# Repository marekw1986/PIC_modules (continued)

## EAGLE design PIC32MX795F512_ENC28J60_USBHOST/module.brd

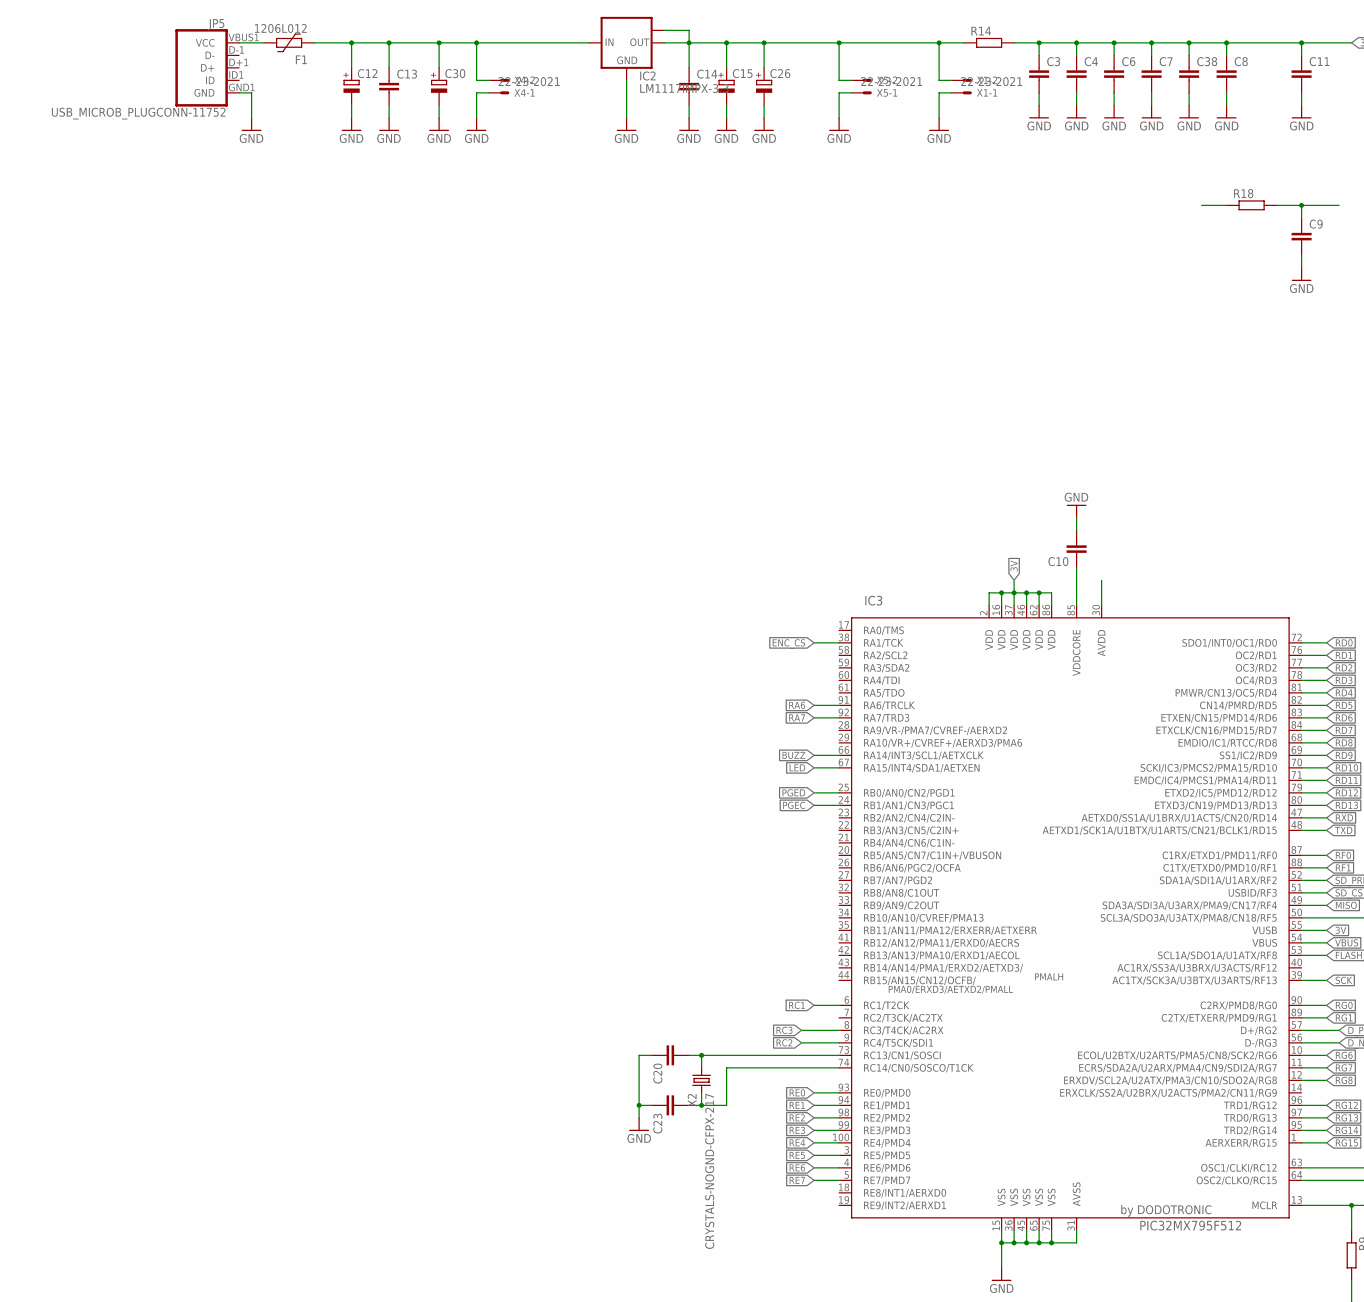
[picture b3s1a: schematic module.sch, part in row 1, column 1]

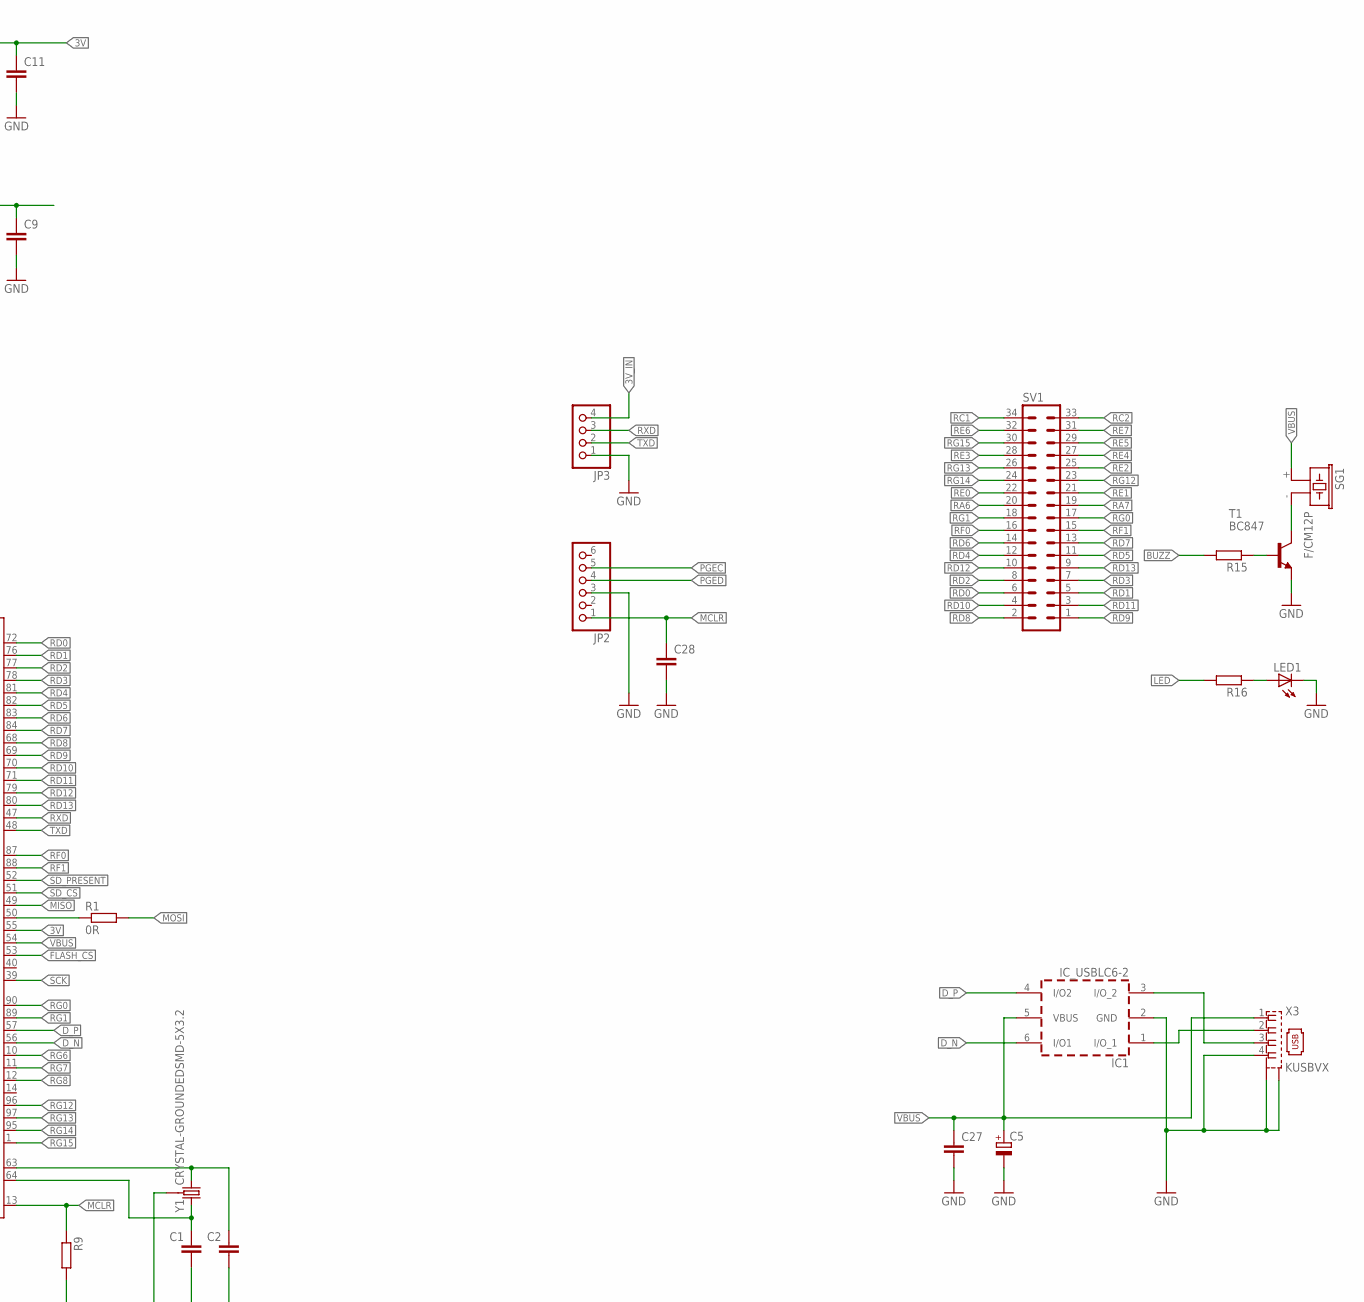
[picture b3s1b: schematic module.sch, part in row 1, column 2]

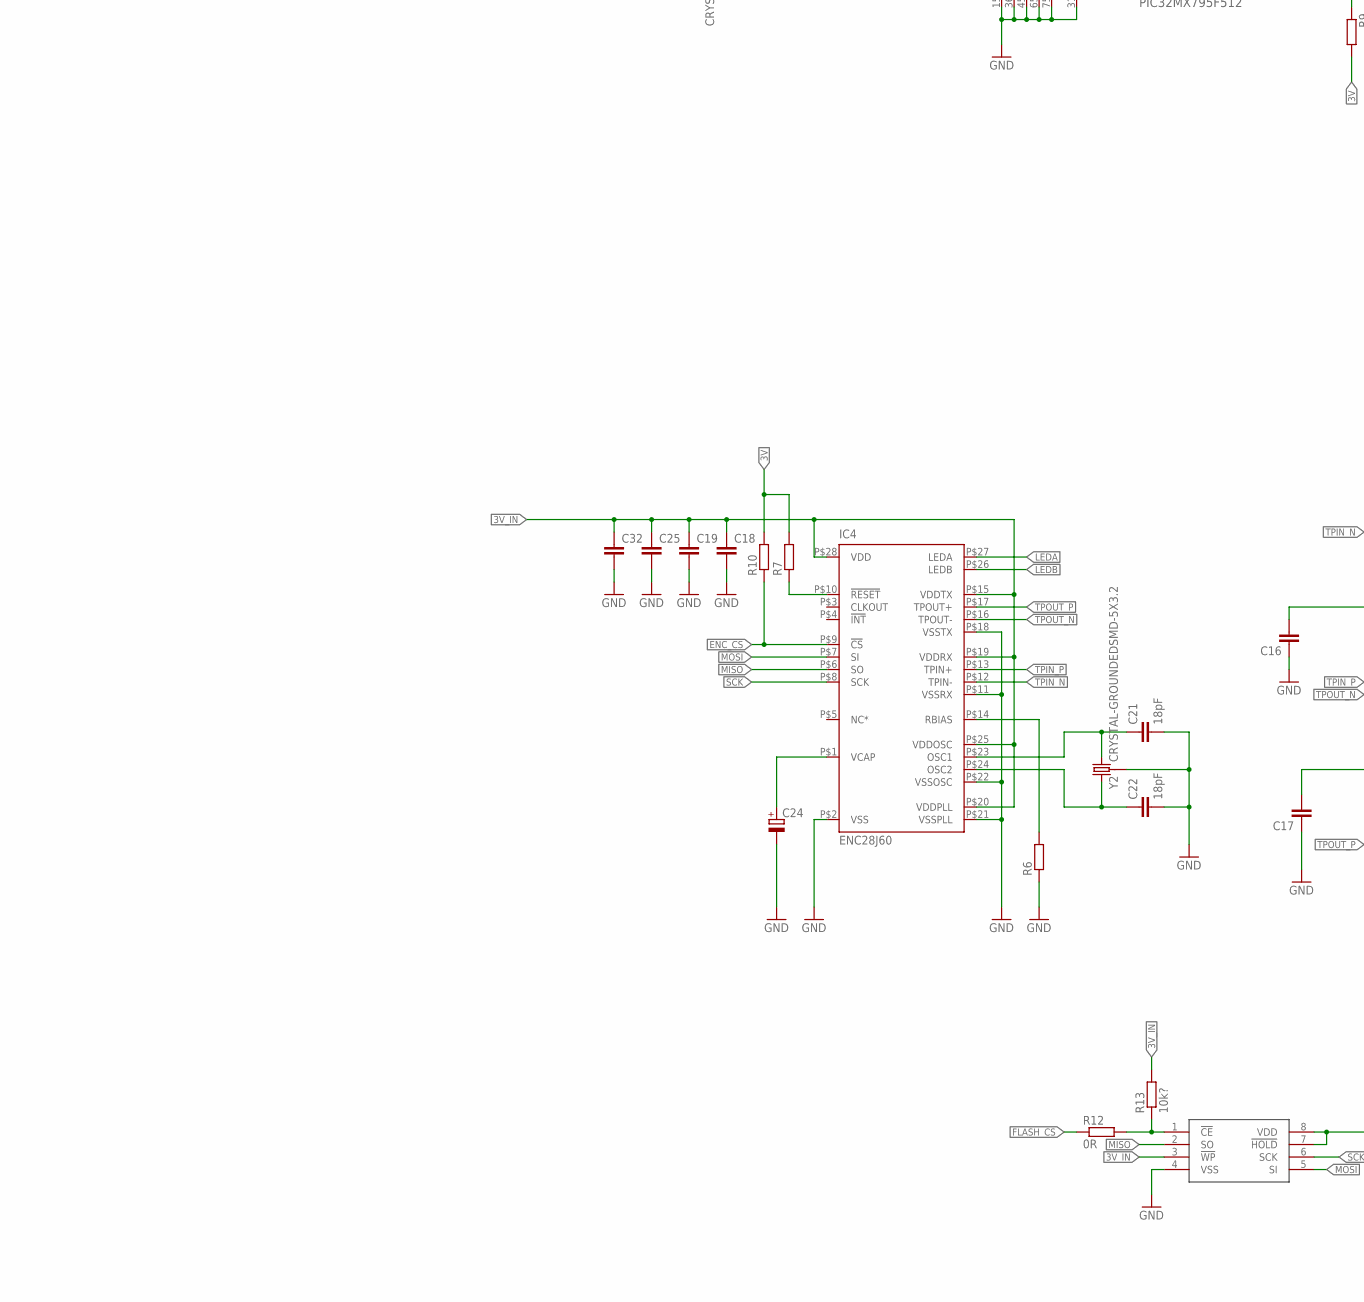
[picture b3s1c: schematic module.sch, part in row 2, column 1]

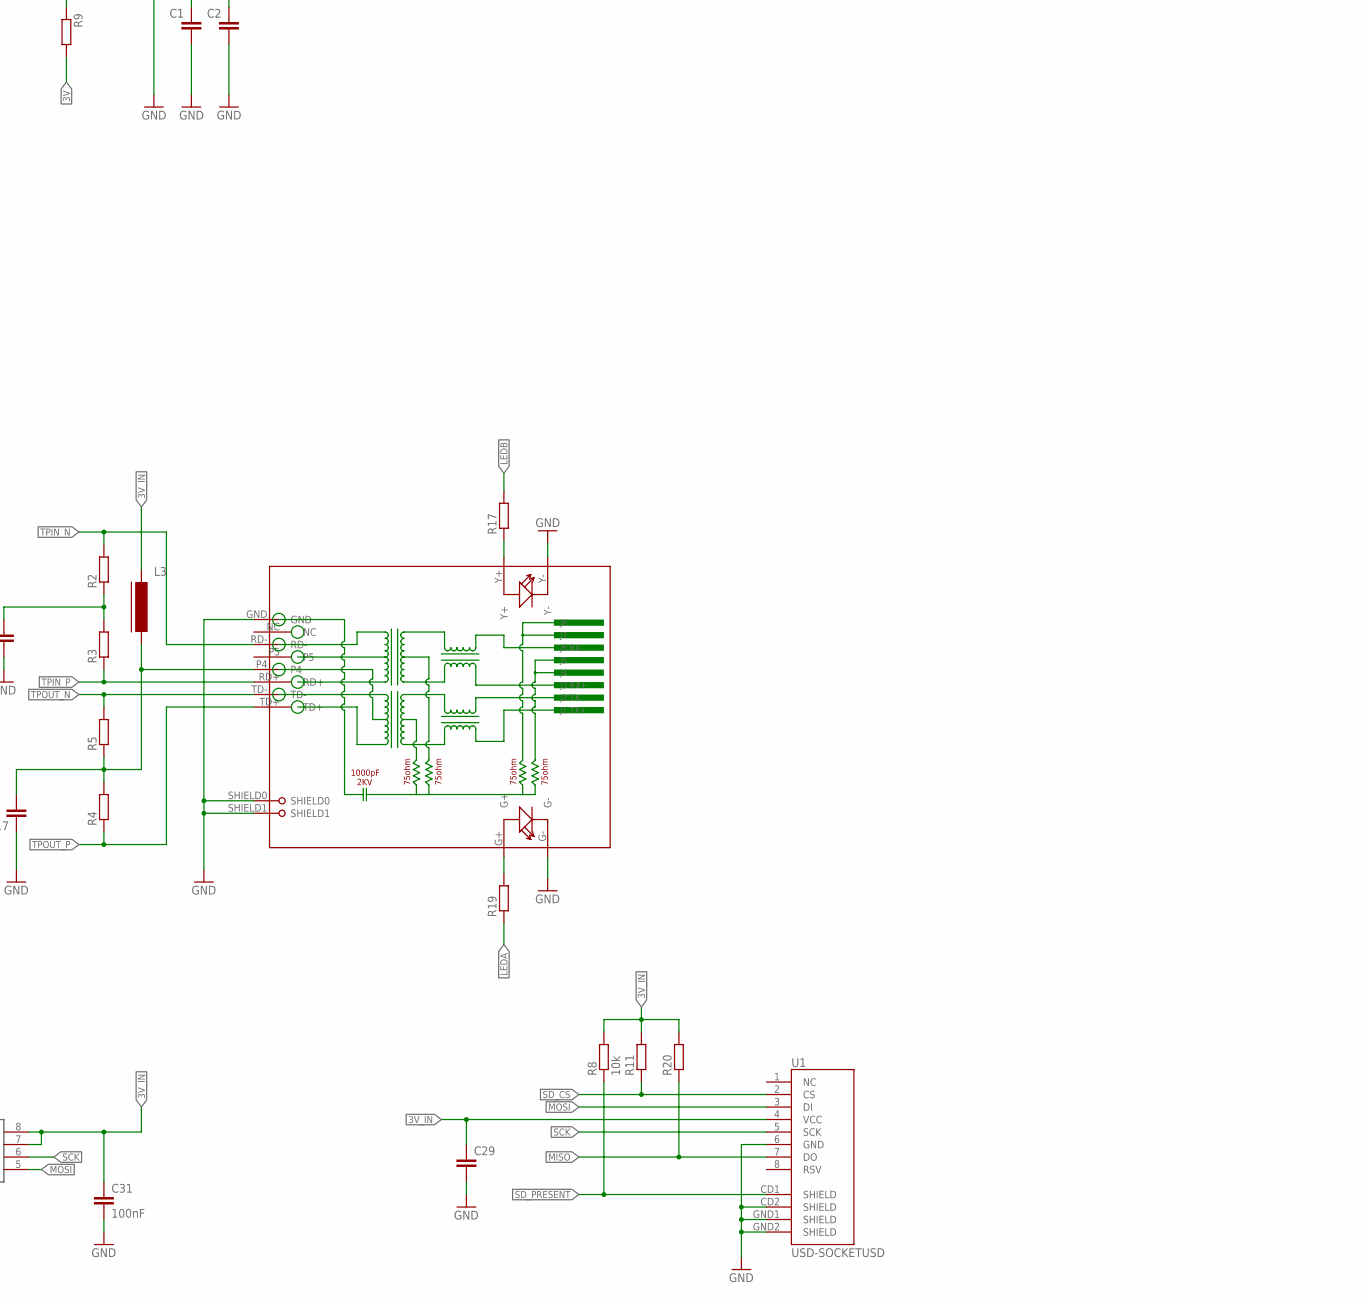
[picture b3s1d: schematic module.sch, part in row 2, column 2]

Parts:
C1, C2, C10, C13, C14, C16, C17, C19, C20, C23, C25, C27, C28, C29, C38: C-EUC0603; C0603
C3, C4, C6, C7, C8, C9, C11, C18, C32: C-EUC0402; C0402
C5, C24, C26, C30: CPOL-EUSMCA; SMC_A
C12, C15: CPOL-EUSMCB; SMC_B
C21, C22: 18pF; C0603
C31: 100nF; C0603
F1: 1206L012; 1206L
IC1: IC_USBLC6-2; SOT-23-6L
IC2: LM1117IMPX-3.3; SOT223
IC3: PIC32MX795F512; TQFP100_12X12
IC4: ENC28J60; TSSOP28W
JP2: PINHD-1X6; 1X06
JP3: PINHD-1X4; 1X04
JP5: USB_MICROB_PLUGCONN-11752; USB-B-MICRO-SMD_V03
L3: FERRITE-0805; FB805
LED1: LED3MM
R1, R12: 0R; R0603
R2, R3, R4, R5, R9, R10, R11, R15, R16, R20: R-EU_R0603; R0603
R6, R18: R-EU_R0805; R0805
R7: R-EU_R0402; R0402
R8: 10k; R0603
R13: 10k?; R0603
R14, R17, R19: R-EU_R1206; R1206
RJ1: HR911105A
SG1: F/CM12P
SV1: ML34L
T1: BC847; SOT23
U1: USD-SOCKETUSD; USD-SOCKET-PP
U$2: SST25VF016BSO8M; SO-08M
X1, X4, X5: 22-23-2021
X2: CRYSTALS-NOGND-CFPX-217; 3.2X1.5-2-PAD
X3: KUSBVX
Y1, Y2: CRYSTAL-GROUNDEDSMD-5X3.2; CRYSTAL-SMD-5X3.2-4PAD

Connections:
3V: C3.1, C4.1, C6.1, C7.1, C8.1, C11.1, C38.1, IC3.2 (VDD), IC3.16 (VDD), IC3.37 (VDD), IC3.46 (VDD), IC3.55 (VUSB), IC3.62 (VDD), IC3.86 (VDD), R7.2, R9.2, R10.2, R14.2, R18.1
3V_IN: C14.1, C15.+, C18.1, C19.1, C25.1, C26.+, C29.1, C31.1, C32.1, IC2.2 (OUT), IC2.TAB (OUT1), IC4.P$15 (VDDTX), IC4.P$19 (VDDRX), IC4.P$20 (VDDPLL), IC4.P$25 (VDDOSC), IC4.P$28 (VDD), JP3.4, L3.1, R8.2, R11.2, R13.2, R14.1, R20.2, U1.4 (VCC), U$2.3 (!WP), U$2.7 (!HOLD), U$2.8 (VDD), X1.2, X5.2
AN_3V: C9.1, IC3.30 (AVDD), R18.2
BUZZ: IC3.66 (RA14/INT3/SCL1/AETXCLK), R15.2
CE1: R12.2, R13.1, U$2.1 (!CE)
D2_N: IC1.1 (I/O_1), X3.2
D2_P: IC1.3 (I/O_2), X3.3
D_N: IC1.6 (I/O1), IC3.56 (D-/RG3)
D_P: IC1.4 (I/O2), IC3.57 (D+/RG2)
ENC_CS: IC3.38 (RA1/TCK), IC4.P$9 (!CS), R10.1
ENC_RST: IC4.P$10 (!RESET), R7.1
FLASH_CS: IC3.53 (SCL1A/SDO1A/U1ATX/RF8), R12.1
GND: C1.2, C2.2, C3.2, C4.2, C5.-, C6.2, C7.2, C8.2, C9.2, C10.2, C11.2, C12.-, C13.2, C14.2, C15.-, C16.1, C17.1, C18.2, C19.2, C20.1, C21.2, C22.2, C23.1, C24.-, C25.2, C26.-, C27.2, C28.2, C29.2, C30.-, C31.2, C32.2, C38.2, IC1.2 (GND), IC2.1 (GND), IC3.15 (VSS), IC3.31 (AVSS), IC3.36 (VSS), IC3.45 (VSS), IC3.65 (VSS), IC3.75 (VSS), IC4.P$2 (VSS), IC4.P$11 (VSSRX), IC4.P$18 (VSSTX), IC4.P$21 (VSSPLL), IC4.P$22 (VSSOSC), JP2.3, JP3.1, JP5.GND1 (GND), LED1.K (C), R6.1, RJ1.G-, RJ1.GND, RJ1.SHIELD0, RJ1.SHIELD1, RJ1.Y-, T1.2 (E), U1.6 (GND), U1.CD2 (SHIELD), U1.GND1 (SHIELD), U1.GND2 (SHIELD), U$2.4 (VSS), X1.1, X3.4, X3.M1 (S1), X3.M2 (S2), X4.1, X5.1, Y1.2 (3), Y1.4 (3), Y2.2 (3), Y2.4 (3)
LED: IC3.67 (RA15/INT4/SDA1/AETXEN), R16.2
LEDA: IC4.P$27 (LEDA), R19.1
LEDB: IC4.P$26 (LEDB), R17.2
MCLR: C28.1, IC3.13 (MCLR), JP2.1, R9.1
MISO: IC3.49 (SDA3A/SDI3A/U3ARX/PMA9/CN17/RF4), IC4.P$6 (SO), R20.1, U1.7 (DO), U$2.2 (SO)
MOSI: IC4.P$7 (SI), R1.2, U1.3 (DI), U$2.5 (SI)
unnamed: SG1.- (2), T1.3 (C)
unnamed: C16.2, R2.1, R3.2
unnamed: R15.1, T1.1 (B)
unnamed: LED1.A, R16.1
unnamed: IC3.50 (SCL3A/SDO3A/U3ATX/PMA8/CN18/RF5), R1.1
unnamed: C17.2, L3.2, R4.2, R5.1, RJ1.P4
unnamed: C10.1, IC3.85 (VDDCORE)
unnamed: IC4.P$14 (RBIAS), R6.2
unnamed: F1.1, JP5.VBUS1 (VCC)
unnamed: C21.1, IC4.P$23 (OSC1), Y2.1 (2)
unnamed: C22.1, IC4.P$24 (OSC2), Y2.3 (1)
unnamed: C24.+, IC4.P$1 (VCAP)
unnamed: R17.1, RJ1.Y+
unnamed: R19.2, RJ1.G+
OSC1: C2.1, IC3.63 (OSC1/CLKI/RC12), Y1.1 (2)
OSC2: C1.1, IC3.64 (OSC2/CLKO/RC15), Y1.3 (1)
PGEC: IC3.24 (RB1/AN1/CN3/PGC1), JP2.5
PGED: IC3.25 (RB0/AN0/CN2/PGD1), JP2.4
RA6: IC3.91 (RA6/TRCLK), SV1.20
RA7: IC3.92 (RA7/TRD3), SV1.19
RC1: IC3.6 (RC1/T2CK), SV1.34
RC2: IC3.9 (RC4/T5CK/SDI1), SV1.33
RC3: IC3.8 (RC3/T4CK/AC2RX)
RD0: IC3.72 (SDO1/INT0/OC1/RD0), SV1.6
RD1: IC3.76 (OC2/RD1), SV1.5
RD2: IC3.77 (OC3/RD2), SV1.8
RD3: IC3.78 (OC4/RD3), SV1.7
RD4: IC3.81 (PMWR/CN13/OC5/RD4), SV1.12
RD5: IC3.82 (CN14/PMRD/RD5), SV1.11
RD6: IC3.83 (ETXEN/CN15/PMD14/RD6), SV1.14
RD7: IC3.84 (ETXCLK/CN16/PMD15/RD7), SV1.13
RD8: IC3.68 (EMDIO/IC1/RTCC/RD8), SV1.2
RD9: IC3.69 (SS1/IC2/RD9), SV1.1
RD10: IC3.70 (SCKI/IC3/PMCS2/PMA15/RD10), SV1.4
RD11: IC3.71 (EMDC/IC4/PMCS1/PMA14/RD11), SV1.3
RD12: IC3.79 (ETXD2/IC5/PMD12/RD12), SV1.10
RD13: IC3.80 (ETXD3/CN19/PMD13/RD13), SV1.9
RE0: IC3.93 (RE0/PMD0), SV1.22
RE1: IC3.94 (RE1/PMD1), SV1.21
RE2: IC3.98 (RE2/PMD2), SV1.25
RE3: IC3.99 (RE3/PMD3), SV1.28
RE4: IC3.100 (RE4/PMD4), SV1.27
RE5: IC3.3 (RE5/PMD5), SV1.29
RE6: IC3.4 (RE6/PMD6), SV1.32
RE7: IC3.5 (RE7/PMD7), SV1.31
RF0: IC3.87 (C1RX/ETXD1/PMD11/RF0), SV1.16
RF1: IC3.88 (C1TX/ETXD0/PMD10/RF1), SV1.15
RG0: IC3.90 (C2RX/PMD8/RG0), SV1.17
RG1: IC3.89 (C2TX/ETXERR/PMD9/RG1), SV1.18
RG6: IC3.10 (ECOL/U2BTX/U2ARTS/PMA5/CN8/SCK2/RG6)
RG7: IC3.11 (ECRS/SDA2A/U2ARX/PMA4/CN9/SDI2A/RG7)
RG8: IC3.12 (ERXDV/SCL2A/U2ATX/PMA3/CN10/SDO2A/RG8)
RG12: IC3.96 (TRD1/RG12), SV1.23
RG13: IC3.97 (TRD0/RG13), SV1.26
RG14: IC3.95 (TRD2/RG14), SV1.24
RG15: IC3.1 (AERXERR/RG15), SV1.30
RXD: IC3.47 (AETXD0/SS1A/U1BRX/U1ACTS/CN20/RD14), JP3.3
SCK: IC3.39 (AC1TX/SCK3A/U3BTX/U3ARTS/RF13), IC4.P$8 (SCK), U1.5 (SCK), U$2.6 (SCK)
SD_CS: IC3.51 (USBID/RF3), R11.1, U1.2 (CS)
SD_PRESENT: IC3.52 (SDA1A/SDI1A/U1ARX/RF2), R8.1, U1.CD1 (SHIELD)
SOSCI: C20.2, IC3.73 (RC13/CN1/SOSCI), X2.1
SOSCO: C23.2, IC3.74 (RC14/CN0/SOSCO/T1CK), X2.2
TPIN_N: IC4.P$12 (TPIN-), R2.2, RJ1.RD-
TPIN_P: IC4.P$13 (TPIN+), R3.1, RJ1.RD+
TPOUT_N: IC4.P$16 (TPOUT-), R5.2, RJ1.TD-
TPOUT_P: IC4.P$17 (TPOUT+), R4.1, RJ1.TD+
TXD: IC3.48 (AETXD1/SCK1A/U1BTX/U1ARTS/CN21/BCLK1/RD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), JP3.2
VBUS: C5.+, C12.+, C13.1, C27.1, C30.+, F1.2, IC1.5 (VBUS), IC2.3 (IN), IC3.54 (VBUS), SG1.+ (1), X3.1, X4.2

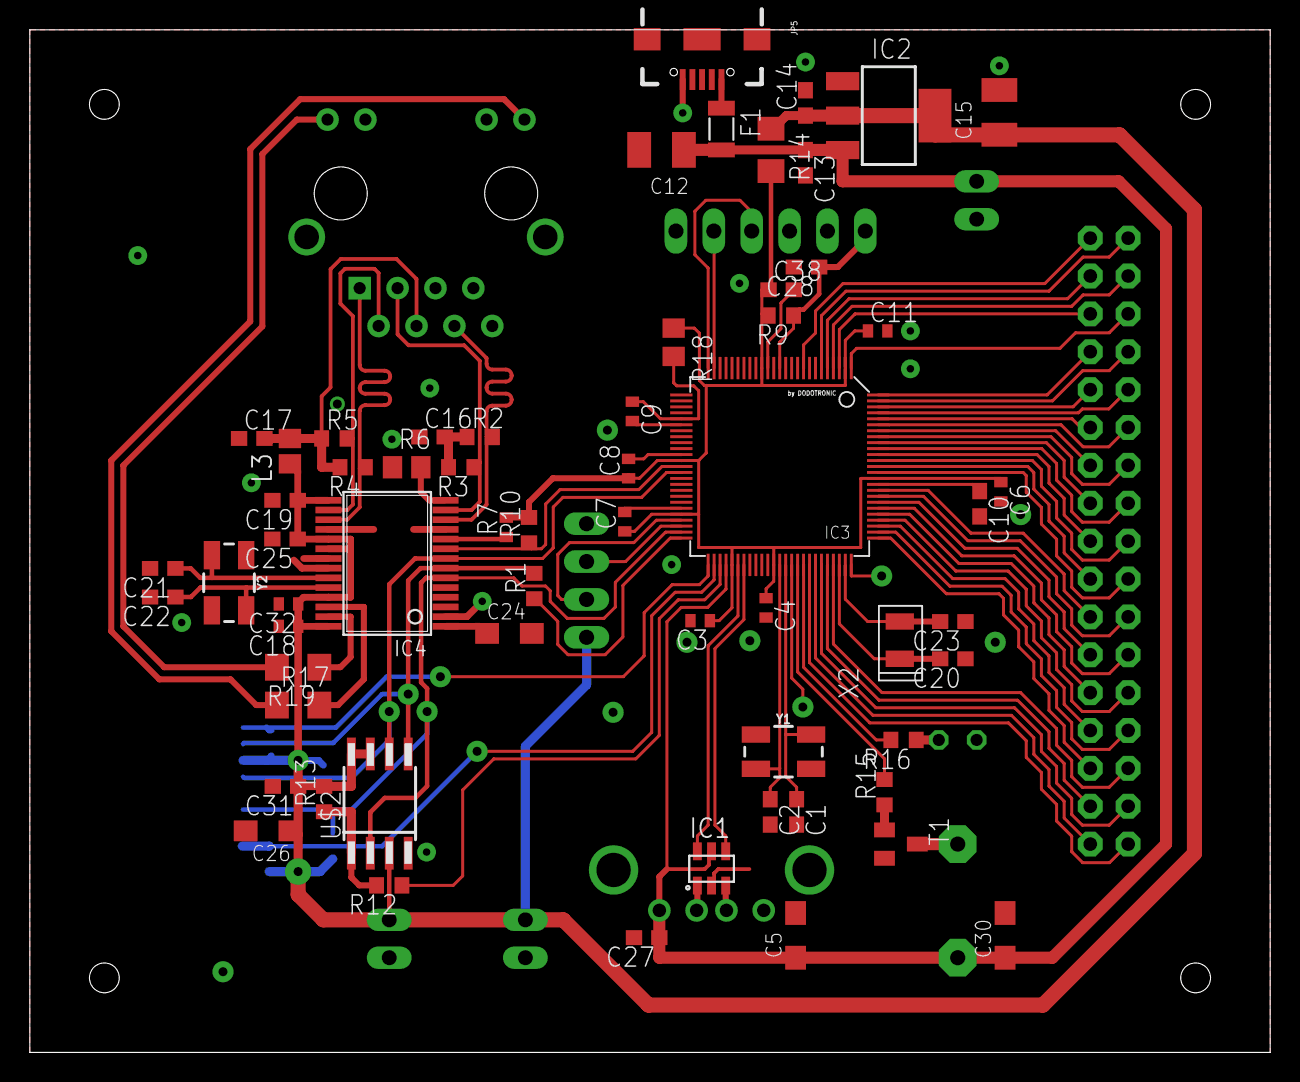
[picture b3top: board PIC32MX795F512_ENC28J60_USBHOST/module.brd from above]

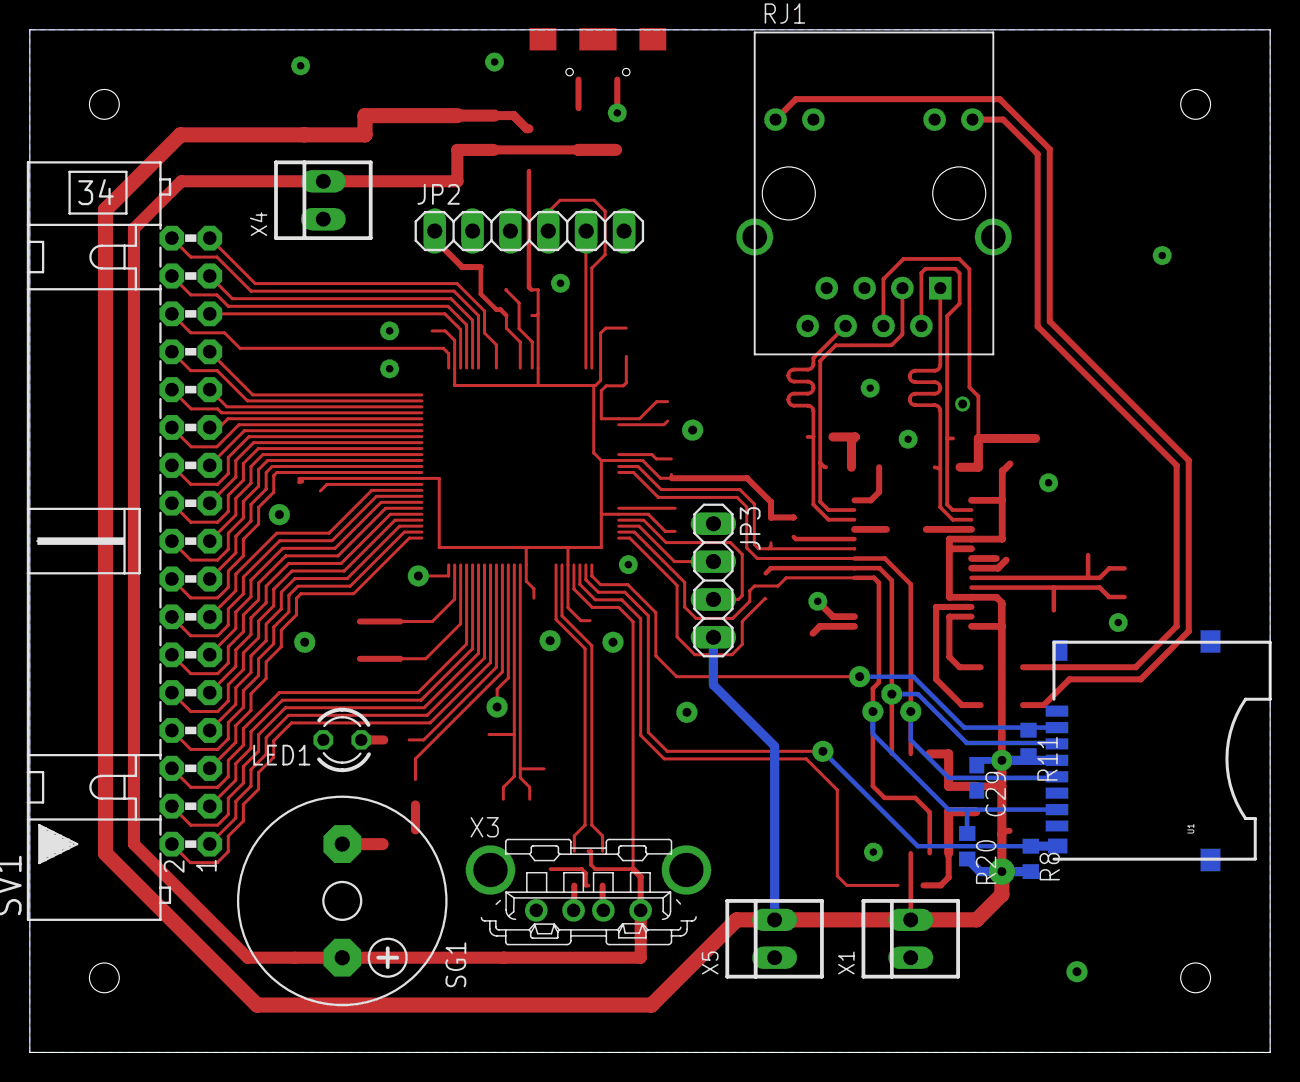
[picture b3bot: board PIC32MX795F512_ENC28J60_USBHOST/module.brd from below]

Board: 2 copper layers, 83.2 x 68.6 mm, 76 parts (15 on the bottom side), 83 nets.

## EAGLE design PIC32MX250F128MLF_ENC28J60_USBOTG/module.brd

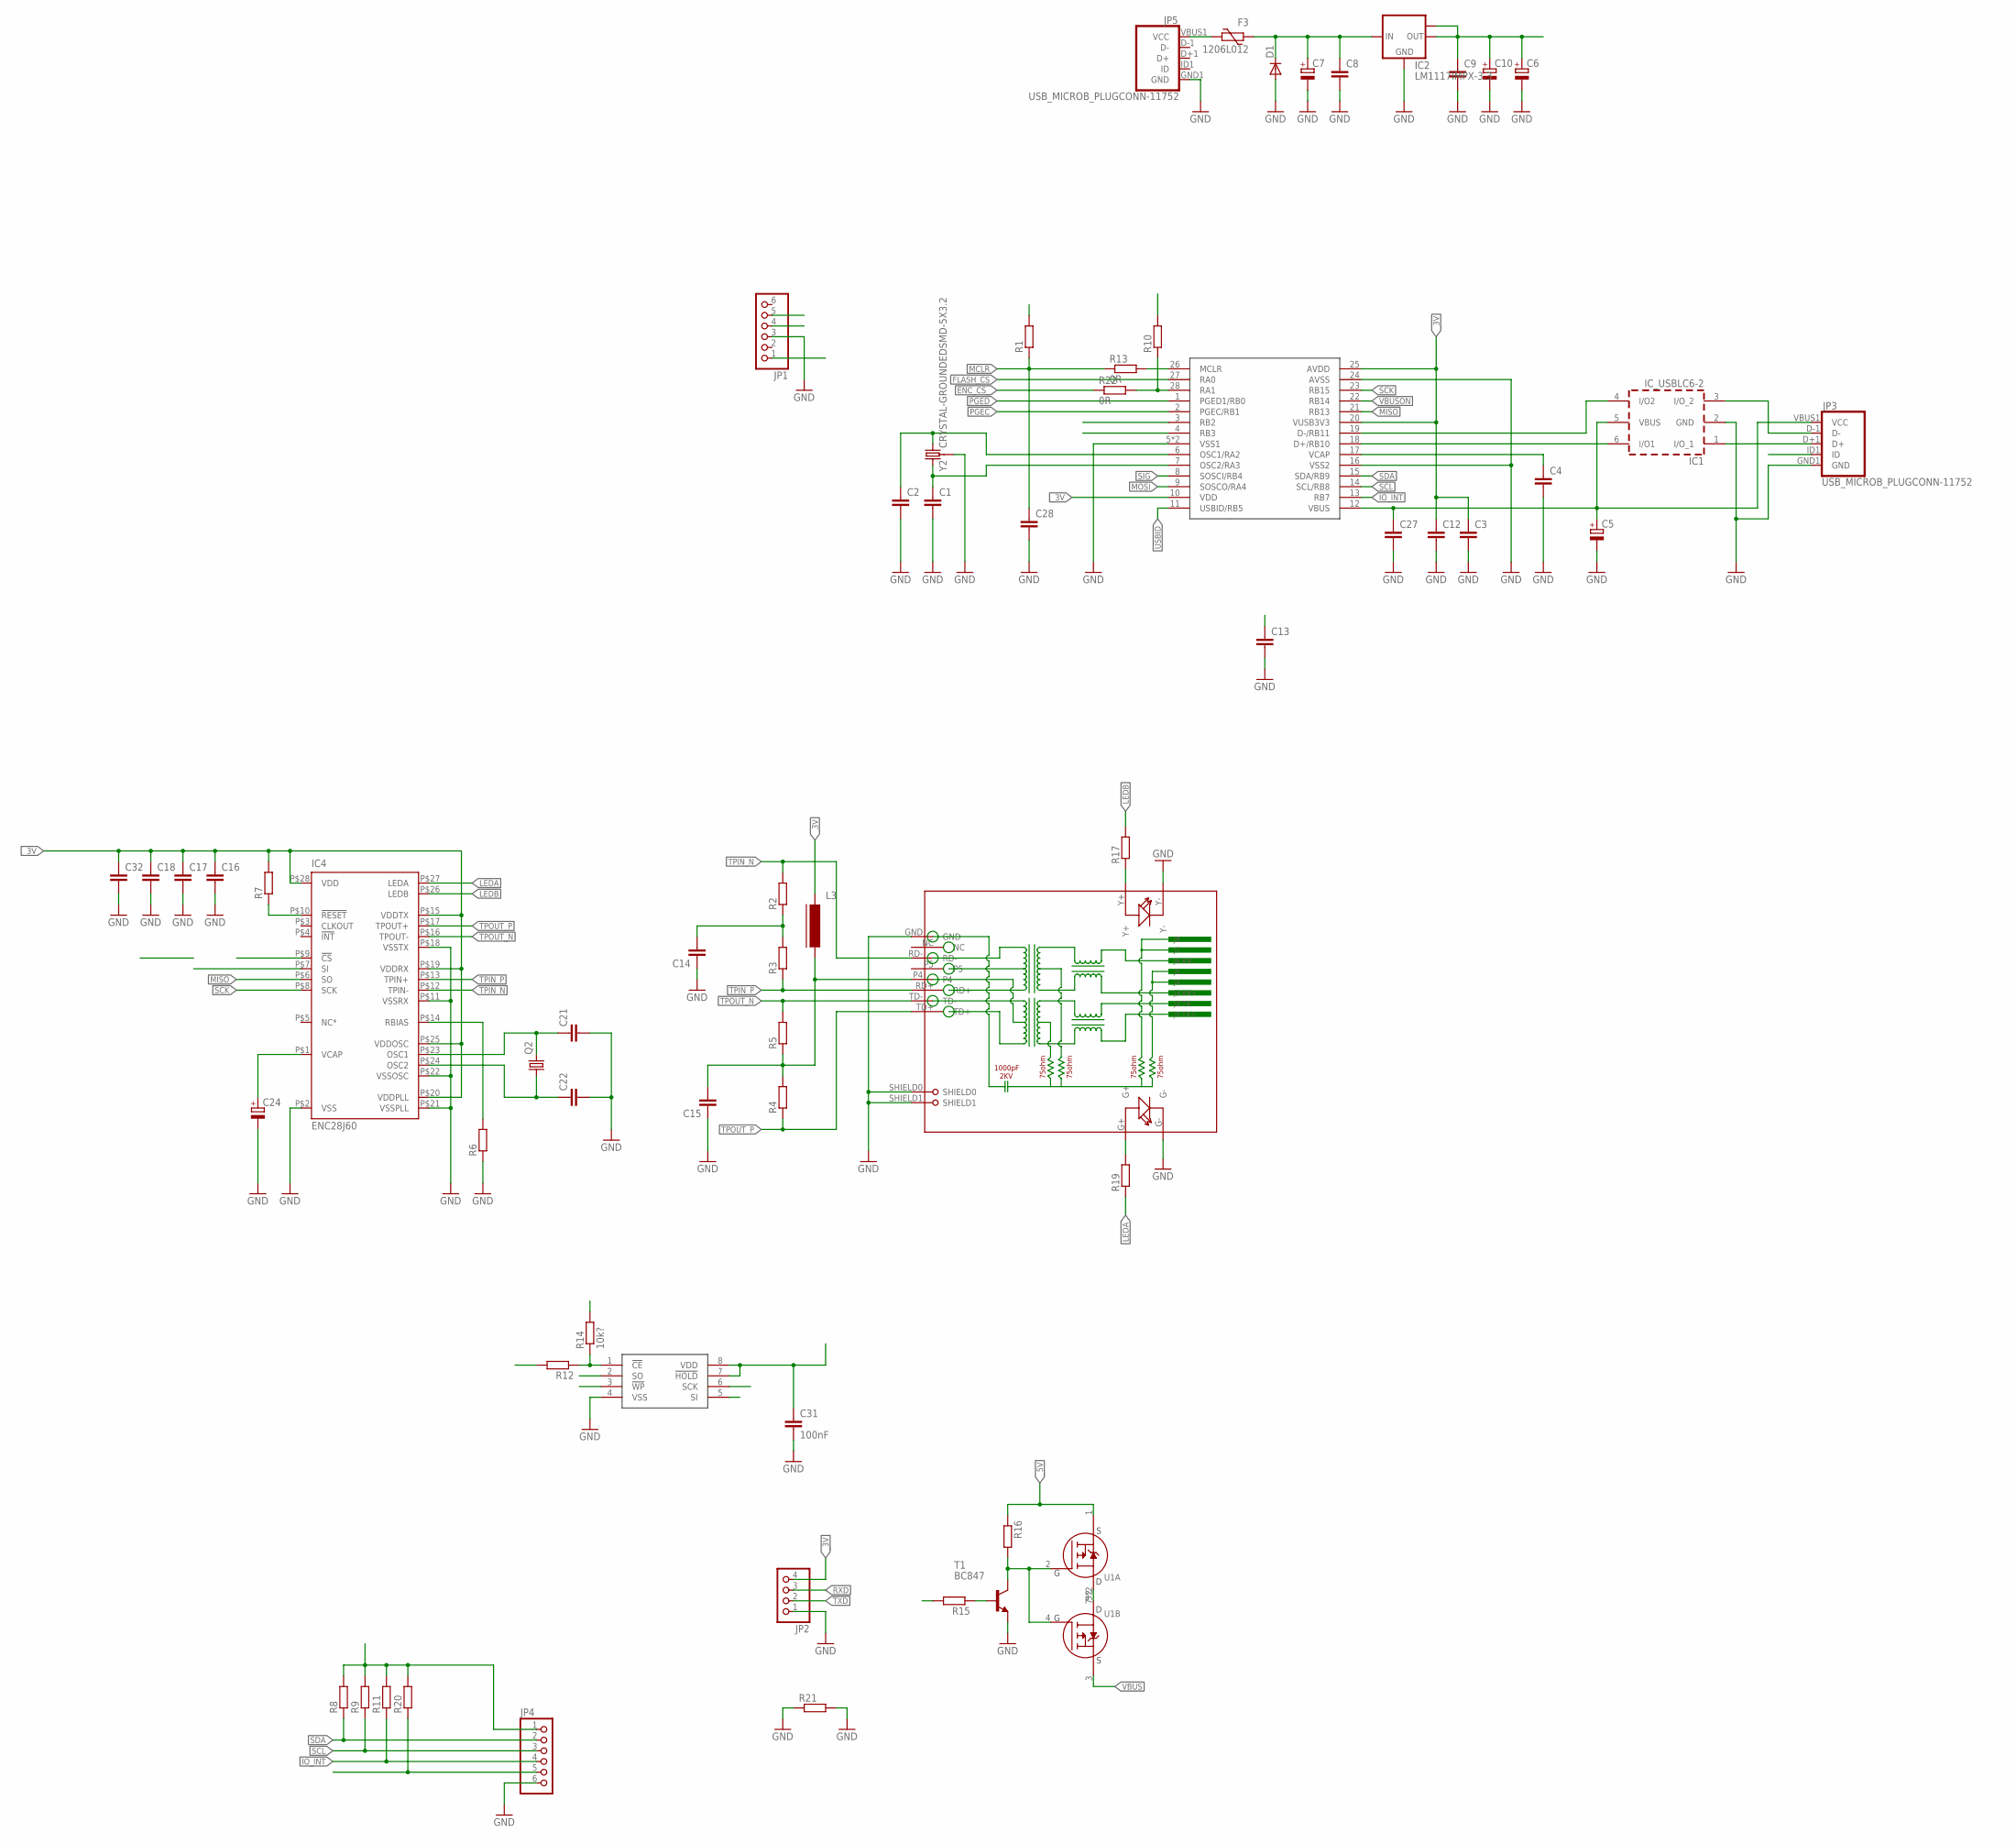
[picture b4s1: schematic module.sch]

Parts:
C1, C2, C4, C8, C9, C12, C13, C14, C15, C21, C22, C27, C28: C-EUC0603; C0603
C3, C16, C17, C18, C32: C-EUC0402; C0402
C5, C6, C24: CPOL-EUSMCA; SMC_A
C7: CPOL-EUSMCC; SMC_C
C10: CPOL-EUSMCB; SMC_B
C31: 100nF; C0603
D1: DIODE-SMB; SMB
F3: 1206L012; 1206L
IC1: IC_USBLC6-2; SOT-23-6L
IC2: LM1117IMPX-3.3; SOT223
IC4: ENC28J60; TSSOP28W
JP1, JP4: PINHD-1X6; 1X06
JP2: PINHD-1X4; 1X04
JP3, JP5: USB_MICROB_PLUGCONN-11752; USB-B-MICRO-SMD_V03
L3: FERRITE-0805; FB805
Q2: CRYSTALHC49S; HC49/S
R1, R2, R3, R4, R5, R7, R8, R9, R10, R11, R12, R15, R20: R-EU_R0603; R0603
R6: R-EU_R0805; R0805
R13, R22: 0R; R0603
R14: 10k?; R0603
R16: R-EU_R0402; R0402
R17, R19, R21: R-EU_R1206; R1206
RJ1: HR911105A
T1: BC847; SOT23
U1: IRF7314_P_MOSFET; SO-8
U$1: PIC32MX250F128B; QFN-S28-6X6
U$2: SST25VF016BSO8M; SO-08M
Y2: CRYSTAL-GROUNDEDSMD-5X3.2; CRYSTAL-SMD-5X3.2-4PAD

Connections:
D_N: IC1.4 (I/O2), U$1.19 (D-/RB11)
D_P: IC1.6 (I/O1), U$1.18 (D+/RB10)
ENC_CS_: IC4.P$9 (!CS), R22.1
ENC_RST: IC4.P$10 (!RESET), R7.1
FLASH_CS: R12.2, U$1.27 (RA0)
GND: C1.2, C2.2, C3.2, C4.2, C5.-, C6.-, C7.-, C8.2, C9.2, C10.-, C12.2, C13.2, C14.1, C15.1, C16.2, C17.2, C18.2, C21.2, C22.2, C24.-, C27.2, C28.2, C31.2, C32.2, D1.A, IC1.2 (GND), IC2.1 (GND), IC4.P$2 (VSS), IC4.P$11 (VSSRX), IC4.P$18 (VSSTX), IC4.P$21 (VSSPLL), IC4.P$22 (VSSOSC), JP1.3, JP2.1, JP3.GND1 (GND), JP4.6, JP5.GND1 (GND), R6.1, R21.1, R21.2, RJ1.G-, RJ1.GND, RJ1.SHIELD0, RJ1.SHIELD1, RJ1.Y-, T1.2 (E), U$1.5 (VSS1), U$1.16 (VSS2), U$1.24 (AVSS), U$1.EXP (VSS1), U$2.4 (VSS), Y2.2 (3), Y2.4 (3)
IO_INT: JP4.4, R11.1, U$1.13 (RB7)
LEDA: IC4.P$27 (LEDA), R19.1
LEDB: IC4.P$26 (LEDB), R17.2
MCLR: C28.1, JP1.1, R1.1, R13.1
MCLR_: R13.2, U$1.26 (MCLR)
MISO: IC4.P$6 (SO), U$1.21 (RB13), U$2.2 (SO)
MOSI: IC4.P$7 (SI), U$1.9 (SOSCO/RA4), U$2.5 (SI)
unnamed: R15.1, T1.1 (B)
unnamed: C14.2, R2.1, R3.2
unnamed: C1.1, U$1.7 (OSC2/RA3), Y2.3 (1)
unnamed: C2.1, U$1.6 (OSC1/RA2), Y2.1 (2)
unnamed: C15.2, L3.2, R4.2, R5.1, RJ1.P4
unnamed: C4.1, U$1.17 (VCAP)
unnamed: F3.1, JP5.VBUS1 (VCC)
unnamed: IC1.1 (I/O_1), JP3.D+1 (D+)
unnamed: IC1.3 (I/O_2), JP3.D-1 (D-)
unnamed: R12.1, R14.1, U$2.1 (!CE)
unnamed: IC4.P$14 (RBIAS), R6.2
unnamed: R16.2, T1.3 (C), U1.2 (G), U1.4 (G)
unnamed: R10.1, R22.2, U$1.28 (RA1)
unnamed: U1.5 (D), U1.6 (D), U1.7 (D), U1.8 (D)
unnamed: C21.1, IC4.P$23 (OSC1), Q2.2
unnamed: C22.1, IC4.P$24 (OSC2), Q2.1
unnamed: C24.+, IC4.P$1 (VCAP)
unnamed: R17.1, RJ1.Y+
unnamed: R19.2, RJ1.G+
PGEC: JP1.5, U$1.2 (PGEC/RB1)
PGED: JP1.4, U$1.1 (PGED1/RB0)
RXD: JP2.3, U$1.3 (RB2)
SCK: IC4.P$8 (SCK), U$1.23 (RB15), U$2.6 (SCK)
SCL: JP4.3, R9.1, U$1.14 (SCL/RB8)
SDA: JP4.2, R8.1, U$1.15 (SDA/RB9)
SIG: JP4.5, R20.1, U$1.8 (SOSCI/RB4)
TPIN_N: IC4.P$12 (TPIN-), R2.2, RJ1.RD-
TPIN_P: IC4.P$13 (TPIN+), R3.1, RJ1.RD+
TPOUT_N: IC4.P$16 (TPOUT-), R5.2, RJ1.TD-
TPOUT_P: IC4.P$17 (TPOUT+), R4.1, RJ1.TD+
TXD: JP2.2, U$1.4 (RB3)
USBID: JP3.ID1 (ID), U$1.11 (USBID/RB5)
VBUS: C5.+, C27.1, IC1.5 (VBUS), JP3.VBUS1 (VCC), U1.3 (S), U$1.12 (VBUS)
VBUSON: R15.2, U$1.22 (RB14)
_3V: C3.1, C6.+, C9.1, C10.+, C12.1, C13.1, C16.1, C17.1, C18.1, C31.1, C32.1, IC2.2 (OUT), IC2.TAB (OUT1), IC4.P$15 (VDDTX), IC4.P$19 (VDDRX), IC4.P$20 (VDDPLL), IC4.P$25 (VDDOSC), IC4.P$28 (VDD), JP2.4, JP4.1, L3.1, R1.2, R7.2, R8.2, R9.2, R10.2, R11.2, R14.2, R20.2, U$1.10 (VDD), U$1.20 (VUSB3V3), U$1.25 (AVDD), U$2.3 (!WP), U$2.7 (!HOLD), U$2.8 (VDD)
_5V: C7.+, C8.1, D1.C, F3.2, IC2.3 (IN), R16.1, U1.1 (S)
